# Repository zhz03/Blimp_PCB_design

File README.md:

# Blimp_PCB_design

The version 2 PCB board layout:

The version 2 PCB schematics:

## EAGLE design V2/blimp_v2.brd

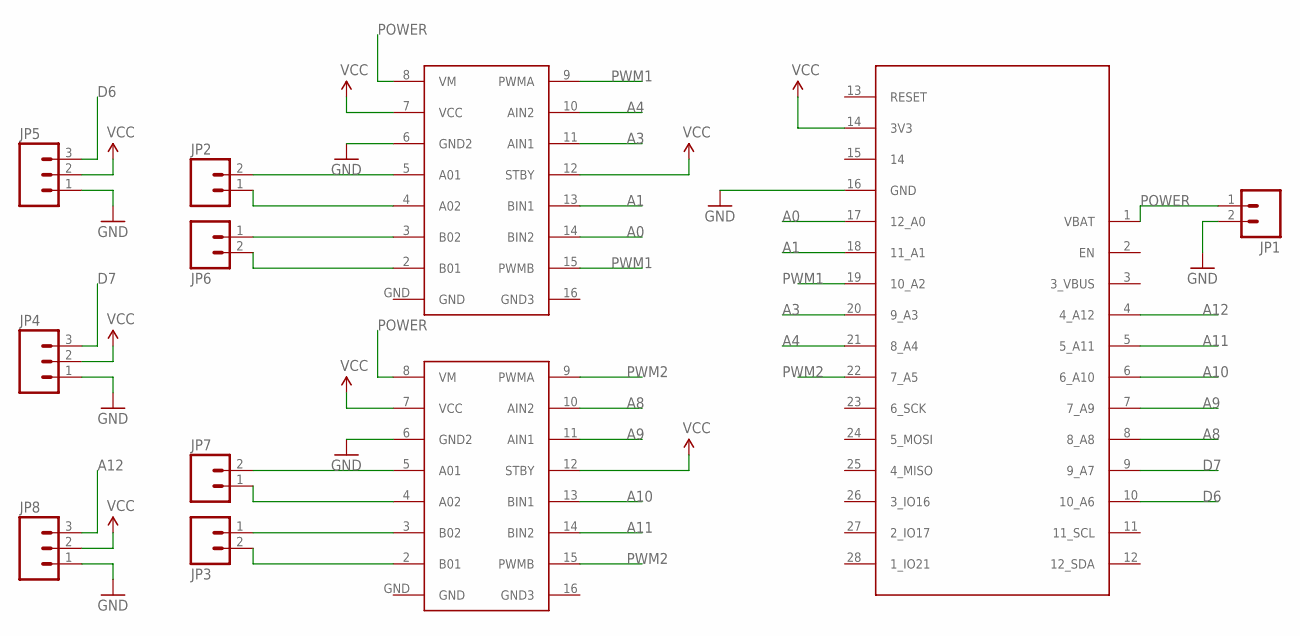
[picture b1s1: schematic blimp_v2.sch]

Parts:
JP1: M02-JST-2MM-SMT; JST-2-SMD
JP2, JP3, JP6, JP7: M02PTH; 1X02
JP4, JP5, JP8: M03PTH; 1X03
U$1: ESP32
U$2, U$4: TB6612

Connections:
A0: U$1.17 (12_A0), U$4.14 (BIN2)
A1: U$1.18 (11_A1), U$4.13 (BIN1)
A3: U$1.20 (9_A3), U$4.11 (AIN1)
A4: U$1.21 (8_A4), U$4.10 (AIN2)
A8: U$1.8 (8_A8), U$2.10 (AIN2)
A9: U$1.7 (7_A9), U$2.11 (AIN1)
A10: U$1.6 (6_A10), U$2.13 (BIN1)
A11: U$1.5 (5_A11), U$2.14 (BIN2)
A12: JP8.3, U$1.4 (4_A12)
D6: JP5.3, U$1.10 (10_A6)
D7: JP4.3, U$1.9 (9_A7)
GND: JP1.2, JP4.1, JP5.1, JP8.1, U$1.16 (GND), U$2.6 (GND2), U$4.6 (GND2)
unnamed: JP2.2, U$4.5 (A01)
unnamed: JP2.1, U$4.4 (A02)
unnamed: JP7.2, U$2.5 (A01)
unnamed: JP7.1, U$2.4 (A02)
unnamed: JP6.1, U$4.3 (B02)
unnamed: JP6.2, U$4.2 (B01)
unnamed: JP3.1, U$2.3 (B02)
unnamed: JP3.2, U$2.2 (B01)
POWER: JP1.1, U$1.1 (VBAT), U$2.8 (VM), U$4.8 (VM)
PWM1: U$1.19 (10_A2), U$4.9 (PWMA), U$4.15 (PWMB)
PWM2: U$1.22 (7_A5), U$2.9 (PWMA), U$2.15 (PWMB)
VCC: JP4.2, JP5.2, JP8.2, U$1.14 (3V3), U$2.7 (VCC), U$2.12 (STBY), U$4.7 (VCC), U$4.12 (STBY)

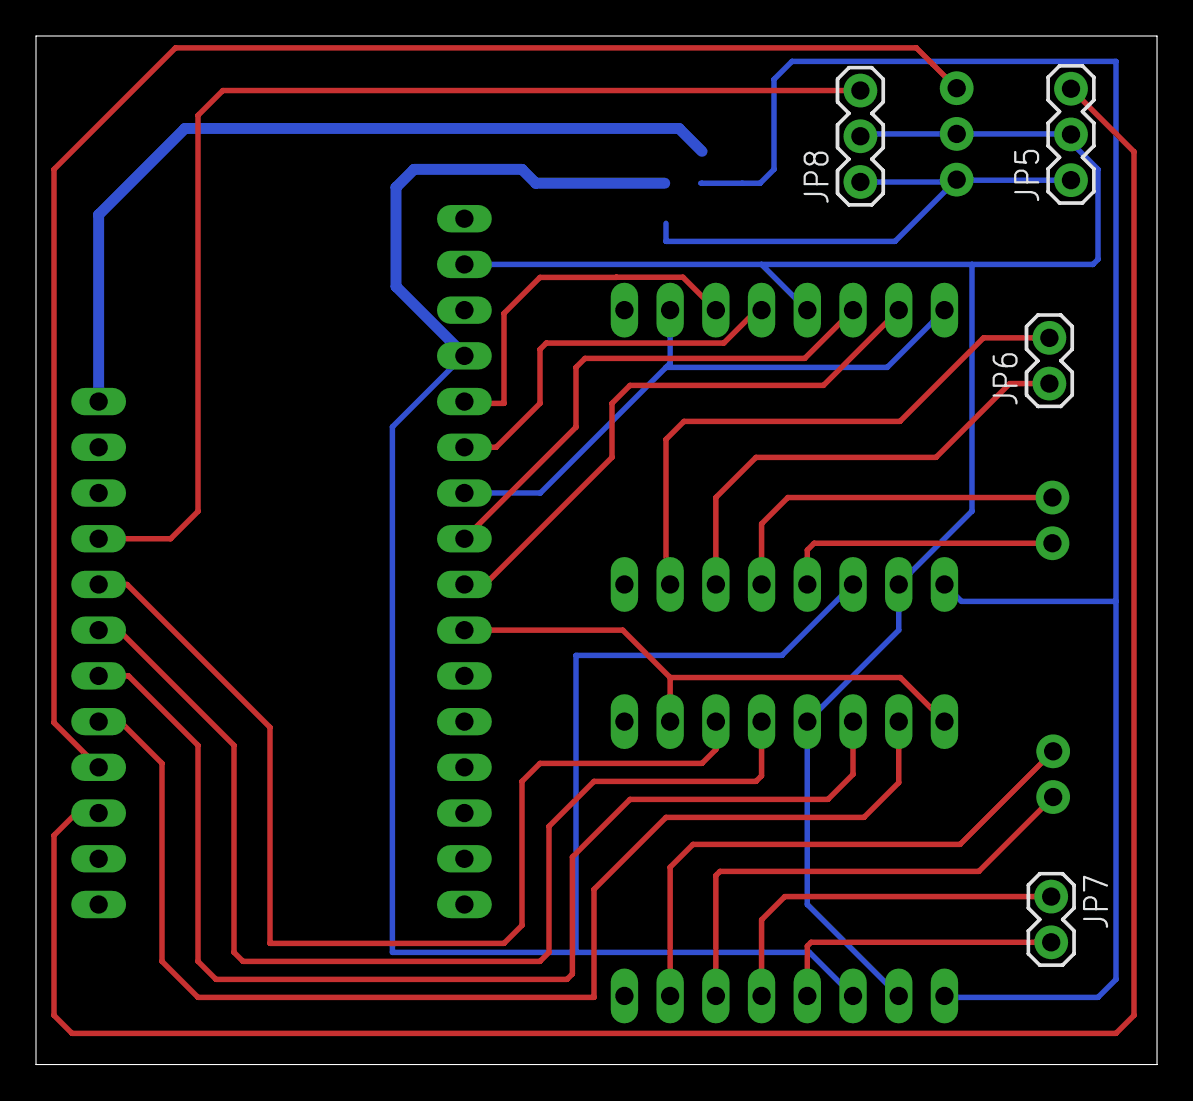
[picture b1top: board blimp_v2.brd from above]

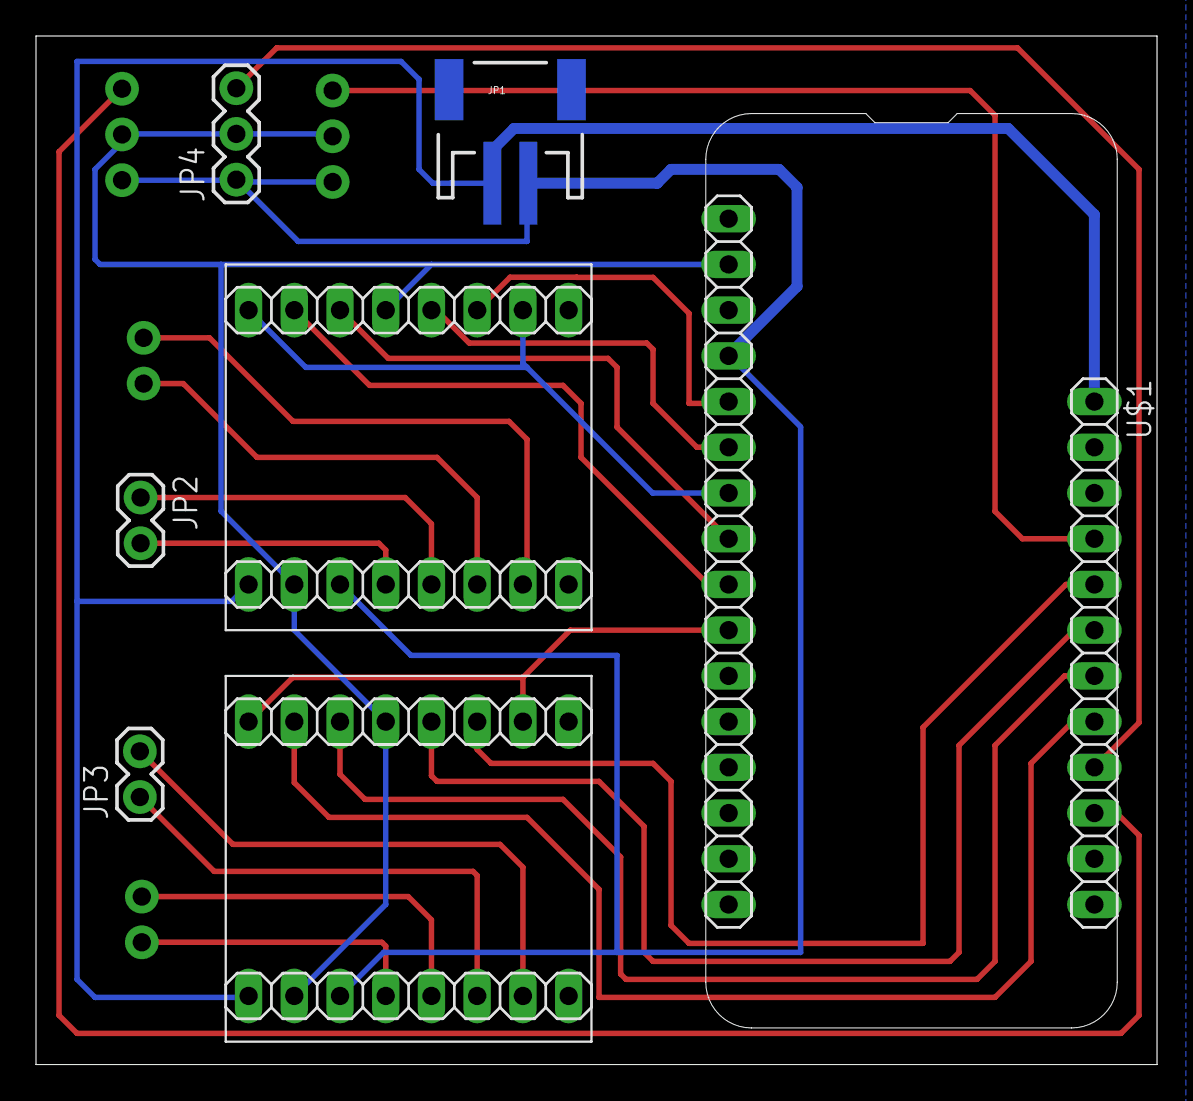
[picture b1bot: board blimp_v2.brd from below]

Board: 2 copper layers, 62.3 x 57.1 mm, 11 parts (7 on the bottom side), 24 nets.

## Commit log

2021-06-09 uploaded blimp v1 PCB and modified design
2021-06-09 upload blimp v2 design
2021-06-09 upload v2 figs
2021-06-09 add PCB v2 preview
2021-06-10 upload the finished routing pcb design
2021-06-10 add one more servo motor pinout

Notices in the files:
parts and their libraries:
SparkFun: Licensing: CC v3.0 Share-Alike You are welcome to use this library for commercial purposes.
SparkFun-Aesthetics: Licensing: Creative Commons ShareAlike 4.0 International - https://creativecommons.org/licenses/by-sa/4.0
